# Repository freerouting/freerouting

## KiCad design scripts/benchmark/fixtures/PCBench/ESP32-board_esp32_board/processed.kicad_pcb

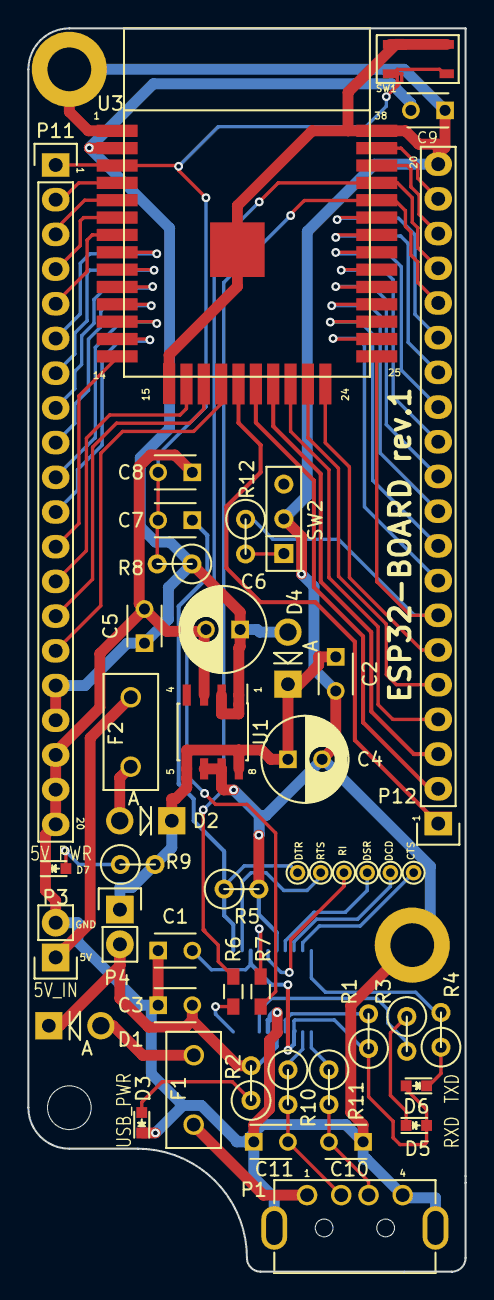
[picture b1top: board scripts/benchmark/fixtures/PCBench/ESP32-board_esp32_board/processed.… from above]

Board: 2 copper layers, 32.0 x 91.0 mm, 48 parts (1 on the bottom side), 63 nets.

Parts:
C1, C2, C3, C5, C7, C8, C9: 0.1u; C_Disc_D3_P2.5
C4, C6: 100u; C_Radial_D6.3_L11.2_P2.5
C10, C11: 47p; C_Disc_D3_P2.5
D1, D2: D; Diode_DO-41_SOD81_Vertical_AnodeUp
D3, D5, D6, D7: LED; LED_0603
D4: D_Schottky; Diode_DO-41_SOD81_Vertical_AnodeUp
F1, F2: FUSE; Fuse_TE5_Littlefuse-395Series
P1: USB_A
P3, P4: CONN_01X02; Pin_Header_Straight_1x02
P5, P6, P7, P8, P9, P10: CONN_01X01; PINTST
P11, P12: CONN_01X20; Pin_Header_Straight_1x20
R1, R8, R12: 10k; R1
R2, R3, R4, R5, R9: 1k; R1
R6, R7: 0; R_0603_HandSoldering
R10, R11: 27; R1
SW1: SW_PUSH; ALPS_SMD_SW
SW2: SPST; SW_Micro_SPST
U1: LT1963A_3.3V; SOIC-8_3.9x4.9mm_Pitch1.27mm
U2: FT231X; FT321X_SSOP
U3: ESP-WROOM-32

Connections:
+3.3VP: C1.2, D5.2, D6.2, R1.1, U2.3, U2.13
+3V3: C5.1, C6.1, C9.2, D4.2, P11.16, P11.17, R8.1, U1.1, U1.2, U3.2
+5V: C2.1, C4.1, D2.1, D4.1, P4.1, R9.2, U1.5, U1.8
+5VD: C3.2, D1.1, P4.2, R2.2, U2.15
CLK: P12.2, U3.20
CMD: P12.1, U3.19
CTS: P9.1, U2.9
DCD: P6.1, U2.8
DSR: P7.1, U2.7
DTR: C7.1, P8.1, R5.1, U2.1
EN: C7.2, C8.2, P11.1, R8.2, SW1.2, U3.3
ESP_RXD: P12.16, R6.1, U3.34
ESP_TXD: P12.17, R7.1, U3.35
GND: C1.1, C2.2, C3.1, C4.2, C5.2, C6.2, C8.1, C9.1, C10.1, C11.1, D3.1, D7.1, P1.4, P1.5, P3.2, P11.18, P11.19, P11.20, P12.20, R5.2, SW1.1, SW2.2, U1.3, U1.6, U1.7, U2.6, U2.16, U3.1, U3.15, U3.38
IO0: P12.7, R12.1, U3.25
IO2: P12.6, U3.24
IO4: P12.8, U3.26
IO5: P12.11, U3.29
IO12: P11.12, U3.14
IO13: P11.13, U3.16
IO14: P11.11, U3.13
IO15: P12.5, U3.23
IO16: P12.9, U3.27
IO17: P12.10, U3.28
IO18: P12.12, U3.30
IO19: P12.13, U3.31
IO21: P12.15, U3.33
IO22: P12.18, U3.36
IO23: P12.19, U3.37
IO25: P11.8, U3.10
IO26: P11.9, U3.11
IO27: P11.10, U3.12
IO32: P11.6, U3.8
IO33: P11.7, U3.9
IO34: P11.4, U3.6
IO35: P11.5, U3.7
NC: P12.14, U3.32
unnamed: C10.2, P1.3, R11.2
unnamed: C11.2, P1.2, R10.2
unnamed: D1.2, F1.2
unnamed: D2.2, F2.2
unnamed: D3.2, R2.1
unnamed: D5.1, R3.1
unnamed: D6.1, R4.1
unnamed: D7.2, R9.1
unnamed: F1.1, P1.1
unnamed: F2.1, P3.1
unnamed: R1.2, U2.14
unnamed: R3.2, U2.17
unnamed: R4.2, U2.10
unnamed: R6.2, U2.20
unnamed: R7.2, U2.4
unnamed: R10.1, U2.12
unnamed: R11.1, U2.11
unnamed: R12.2, SW2.1
RI: P5.1, U2.5
RTS: P10.1, U2.2
SD0: P12.3, U3.21
SD1: P12.4, U3.22
SD2: P11.14, U3.17
SD3: P11.15, U3.18
SENSOR_VN: P11.3, U3.5
SENSOR_VP: P11.2, U3.4

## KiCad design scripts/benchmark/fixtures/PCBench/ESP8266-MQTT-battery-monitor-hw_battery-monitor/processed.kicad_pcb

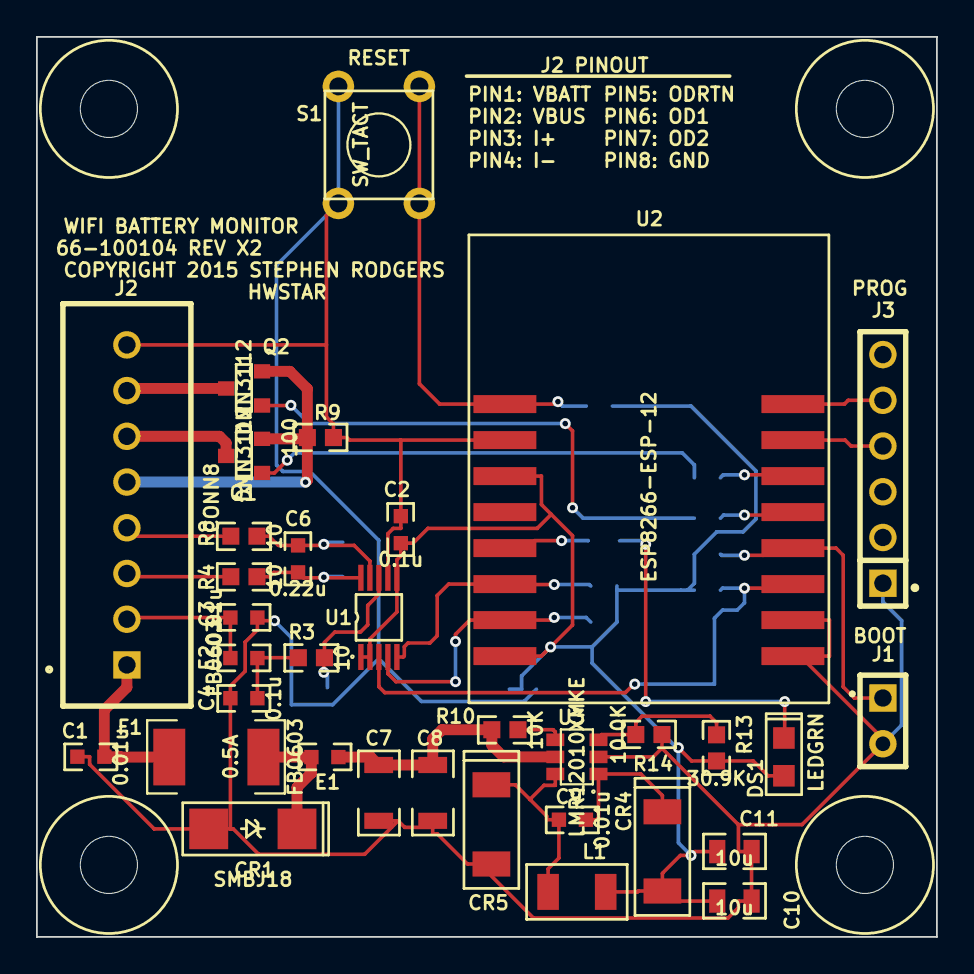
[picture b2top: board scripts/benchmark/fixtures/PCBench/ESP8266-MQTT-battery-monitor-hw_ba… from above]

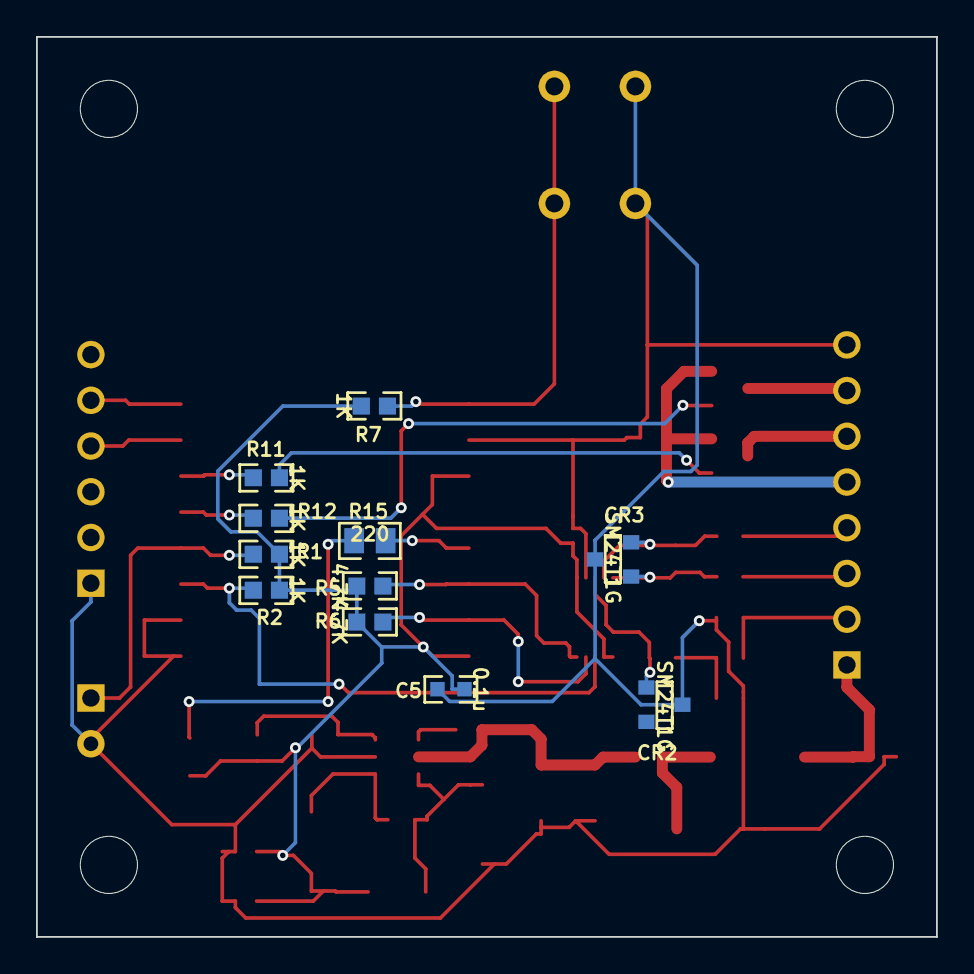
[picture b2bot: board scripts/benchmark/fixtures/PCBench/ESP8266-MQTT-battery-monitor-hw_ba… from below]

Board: 2 copper layers, 50.0 x 50.0 mm, 49 parts (11 on the bottom side), 32 nets.

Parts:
C1, C3, C9: 0.01u; CC0603
C2, C4, C5: 0.1u; CC0603
C6: 0.22u; CC0603
C7, C8: 10u; CC1206
C10, C11: 10u; CC0805
CR1: SMBJ18; SMB-SAR
CR2, CR3: SM24T1G; SOT23-3-SAR
CR4, CR5: CMS06; M-FLAT-SAR
DS1: LEDGRN; LED0805
E1, E2: FB0603; CC0603
F1: 0.5A; MINISMD1812
J1: CONN2; BERG2
J2: CONN8; PHOENIX254-8
J3: CONN6; BERG6
L1: 10uH; IND1210
MTG-HOLE-125-RING-300, MTG-HOLE-125-RING-300_2, MTG-HOLE-125-RING-300_3, MTG-HOLE-125-RING-300_4: VAL**; MTG-HOLE-125-RING-300
Q1, Q2: DMN3112; SOT23-3-SAR
R1, R2, R7, R11, R12: 1K; RC0603
R3, R4, R8: 10; RC0603
R5, R6: 4.7K; RC0603
R9: 100; RC0603
R10: 10K; RC0603
R13: 30.9K; RC0603
R14: 10.0K; RC0603
R15: 220; RC0805
S1: SW_TACT; SW_TACT_6MM
U1: INA226; MSOP-10-SAR
U2: ESP8266-ESP-12; ESP8266-ESP12
U3: LMR12010XMKE; SOT23-6-SAR

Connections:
+3.3V: C2.1, C5.1, C10.1, C11.1, CR4.1, DS1.1, L1.2, R1.1, R2.1, R5.1, R6.1, R7.1, R13.1, U1.1, U1.2, U1.6, U2.3, U2.8
/ALERT: R2.2, U1.3, U2.11
/CONNLED: R15.1, U2.5
/OD1: J2.6, Q1.3
/OD2: J2.7, Q2.3
/ODRTN: J2.5, Q1.2, Q2.2, R9.1
/OUT1: R11.2, U2.14
/OUT2: R12.2, U2.13
/RXD: J3.4, U2.15
/SCL: R5.2, U1.5, U2.6
/SDA: R6.2, U1.4, U2.7
/TXD: J3.5, U2.16
/VBIN: C1.1, F1.1, J2.1
/VBINF: CR1.2, E1.1, F1.2
/VBOOST: C9.1, CR4.2, U3.1
/VBUS: CR2.1, R3.1, U1.8
/VFB: R13.2, R14.1, U3.3
/VIN+: C6.1, CR3.1, R4.1, U1.10
/VIN-: C6.2, CR3.2, R8.1, U1.9
/VSW: C9.2, CR5.2, L1.1, U3.6
GND: C1.2, C2.2, C3.2, C4.2, C5.2, C7.2, C8.2, C10.2, C11.2, CR1.1, CR2.3, CR3.3, CR5.1, J1.2, J2.8, J3.1, R9.2, R14.2, S1.1, S1.2, U1.7, U2.2, U2.9, U2.10, U3.2
unnamed: C3.1, E2.1, J2.2
unnamed: C4.1, E2.2, R3.2
unnamed: DS1.2, R15.2
unnamed: J1.1, R1.2, U2.12
unnamed: J2.3, R4.2
unnamed: J2.4, R8.2
unnamed: Q1.1, R11.1
unnamed: Q2.1, R12.1
unnamed: R7.2, S1.3, S1.4, U2.1
unnamed: R10.1, U3.4
VBATT: C7.1, C8.1, E1.2, R10.2, U3.5

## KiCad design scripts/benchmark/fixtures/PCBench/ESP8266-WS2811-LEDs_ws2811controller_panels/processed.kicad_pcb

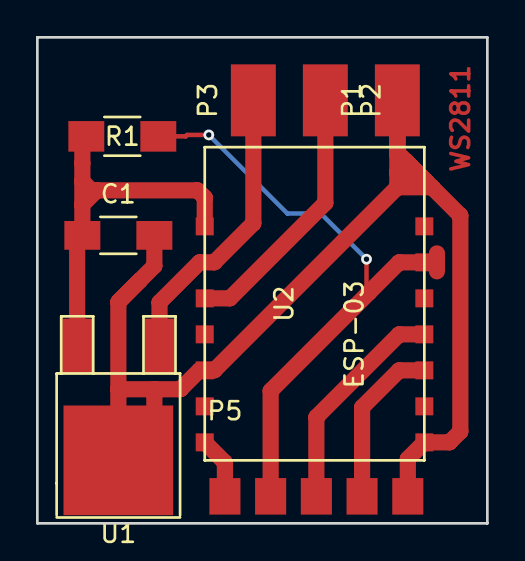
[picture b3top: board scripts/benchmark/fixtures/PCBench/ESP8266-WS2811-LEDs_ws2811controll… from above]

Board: 2 copper layers, 25.0 x 27.0 mm, 8 parts (0 on the bottom side), 8 nets.

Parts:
C1: 22u; C_1206_HandSoldering
P1: PSU_GND; SolderPad
P2: PSU_EN; SolderPad
P3: PSU_5V; SolderPad
P5: DEBUG_HDR; 5pin_SMD
R1: 10K; R_1206_HandSoldering
U1: LF33; TO-252-2Lead
U2: ESP-03; esp-03

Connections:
+3V3: C1.1, R1.2, U1.3, U2.8
+5V: P3.1, U1.1
/CH_PD: P5.2, R1.1, U2.6
/FLASH_EN: P5.1, U2.14
/PSU_EN: P2.1, U2.10
/UART_RX: P5.3, U2.4
/UART_TX: P5.4, U2.3
GND: C1.2, P1.1, P5.5, U1.2, U2.1, U2.12

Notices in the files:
scripts/benchmark/fixtures/PCBench/ESP8266-MQTT-battery-monitor-hw_battery-monitor/processed.kicad_pcb:
COPYRIGHT 2015 STEPHEN RODGERS
